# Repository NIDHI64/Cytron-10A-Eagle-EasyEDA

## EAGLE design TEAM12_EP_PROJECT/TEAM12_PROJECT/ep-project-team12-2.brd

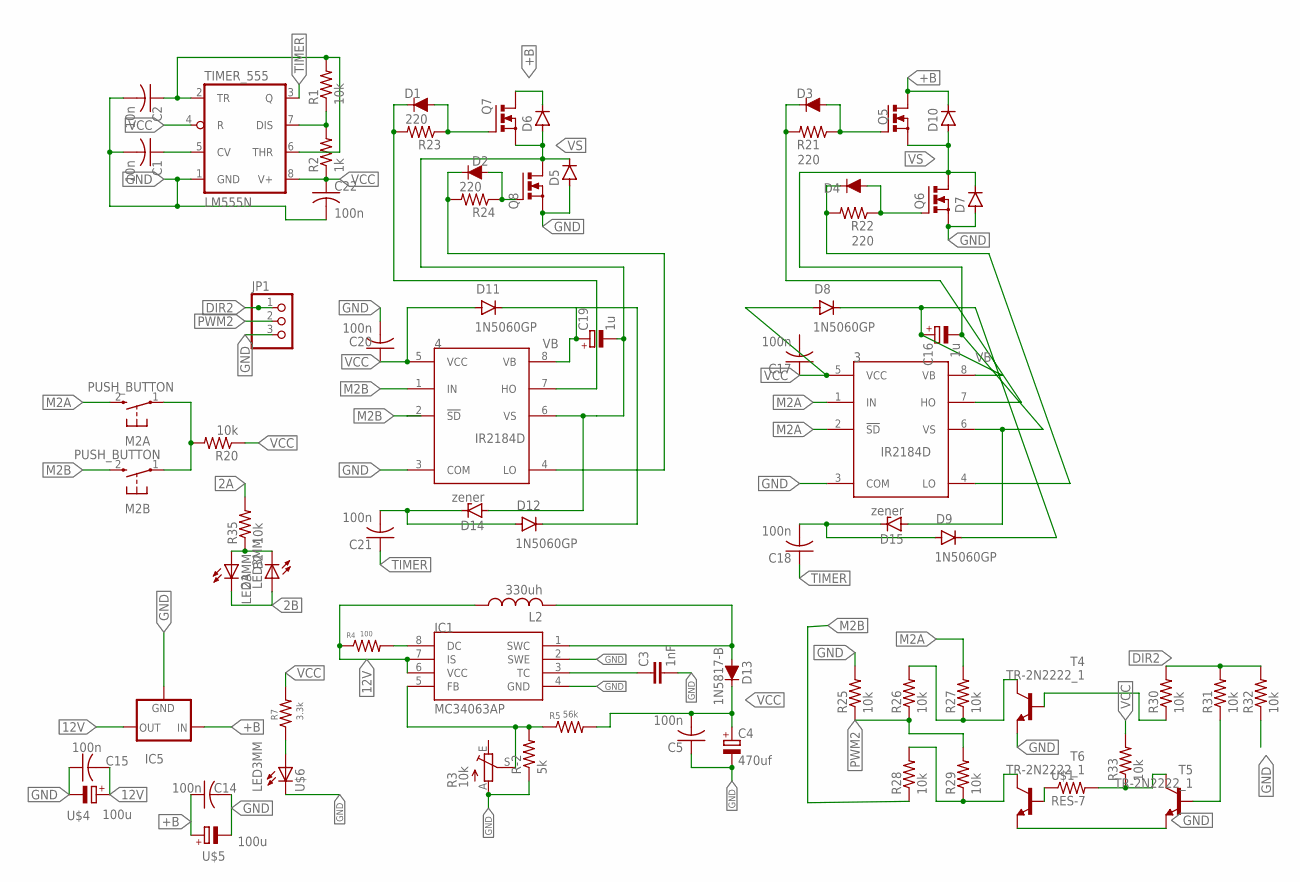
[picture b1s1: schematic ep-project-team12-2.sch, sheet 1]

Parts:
2A: LED3MM
3, 4: IR2184D; DIL08
B2: LED3MM
C1, C2: 10n; C025-025X050
C3: 1nF; C025-025X050
C4: 470uf; E3,5-8
C5, C14, C15, C17, C18, C20, C21, C22: 100n; C025-025X050
C16, C19: 1u; E5-5
D1, D2, D3, D4: 1A/50V/1.1V; DIODE-1N4001
D5, D6, D7, D10: BY396; DO201-15
D8, D9, D11, D12: 1N5060GP; DO15-12
D13: 1N5817-B; DIODE-1N4001
D14, D15: zener; SOD81
IC1: MC34063AP; DIL08
IC5: 78XXS
JP1: PINHD-3_DATA; 1X03_DATA
L2: 330uh; POWER-CHOKE_WE-TPC
M2A, M2B: PUSH_BUTTON; B3F-10XX
Q5, Q6, Q7, Q8: MOSFET_NTO220BV; TO220BV
R1, R20, R25, R26, R27, R28, R29, R30, R31, R32, R33, R35: 10k; 0204/7
R2: 1k; 0204/7
R3: 10k; CA6V
R4: 100; 0204/7
R5: 56k; 0204/7
R7: 3.3k; 0204/7
R21, R22, R23, R24: 220; 0204/7
R-2: 5k; 0204/7
T4, T5, T6: TR-2N2222_1; TO92-EBC
TIMER_555: LM555N; DIL08
U$1: RES-7; 0204/7
U$4, U$5: 100u; E3,5-8
U$6: LED3MM

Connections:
2A: R35.2
2B: 2A.K (C), B2.A
12V: C15.2, IC1.6 (VCC), IC1.7 (IS), IC5.OUT, L2.1, R4.1, U$4.+
+B: C14.1, D6.C, D10.C, IC5.IN, Q5.D, Q7.D, U$5.+
DIR2: JP1.1, R30.2, R31.2, R32.2
GND: 3.3 (COM), 4.3 (COM), C1.2, C2.2, C3.2, C4.-, C5.1, C14.2, C15.1, C20.2, C22.2, D5.A, D7.A, IC1.2 (SWE), IC1.4 (GND), IC5.GND, JP1.3, Q6.S, Q8.S, R3.A, R25.2, R32.1, R-2.1, T4.E, T5.E, T6.E, TIMER_555.1 (GND), U$4.-, U$5.-, U$6.K (C)
M2A: 3.1 (IN), 3.2 (!SD), M2A.2 (S), R27.2
M2B: 4.1 (IN), 4.2 (!SD), M2B.2 (S), R28.1
unnamed: C1.1, TIMER_555.5 (CV)
unnamed: R1.1, R2.2, TIMER_555.7 (DIS)
unnamed: C2.1, R1.2, TIMER_555.2 (TR), TIMER_555.6 (THR)
unnamed: D4.A, Q6.G, R22.1
unnamed: 3.4 (LO), D4.C, R22.2
unnamed: M2A.1, M2B.1, R20.2
unnamed: T6.B, U$1.1
unnamed: C3.1, IC1.3 (TC)
unnamed: D13.A, IC1.1 (SWC), L2.2
unnamed: 4.7 (HO), D1.C, R23.2
unnamed: IC1.5 (FB), R3.S, R5.1, R-2.2
unnamed: 4.4 (LO), D2.C, R24.2
unnamed: IC1.8 (DC), R4.2
unnamed: R7.1, U$6.A
unnamed: D3.A, Q5.G, R21.1
unnamed: 3.7 (HO), D3.C, R21.2
unnamed: C18.2, D9.A, D15.C
unnamed: D2.A, Q8.G, R24.1
unnamed: D1.A, Q7.G, R23.1
unnamed: C21.2, D12.A, D14.C
unnamed: R28.2, R29.1, T6.C
unnamed: R26.2, R27.1, T4.C
unnamed: R30.1, T4.B
unnamed: R33.1, T5.C, U$1.2
unnamed: R31.1, T5.B
unnamed: 2A.A, B2.K (C), R35.1
PWM2: JP1.2, R25.1, R26.1, R29.2
TIMER: C18.1, C21.1, TIMER_555.3 (Q)
VB: 3.8 (VB), 4.8 (VB), C16.+, C19.+, D8.C, D9.C, D11.C, D12.C
VCC: 3.5 (VCC), 4.5 (VCC), C4.+, C5.2, C17.1, C20.1, C22.1, D8.A, D11.A, D13.C, R2.1, R5.2, R7.2, R20.1, R33.2, TIMER_555.4 (R), TIMER_555.8 (V+)
VS: 3.6 (VS), 4.6 (VS), C16.-, C19.-, D5.C, D6.A, D7.C, D10.A, D14.A, D15.A, Q5.S, Q6.D, Q7.S, Q8.D

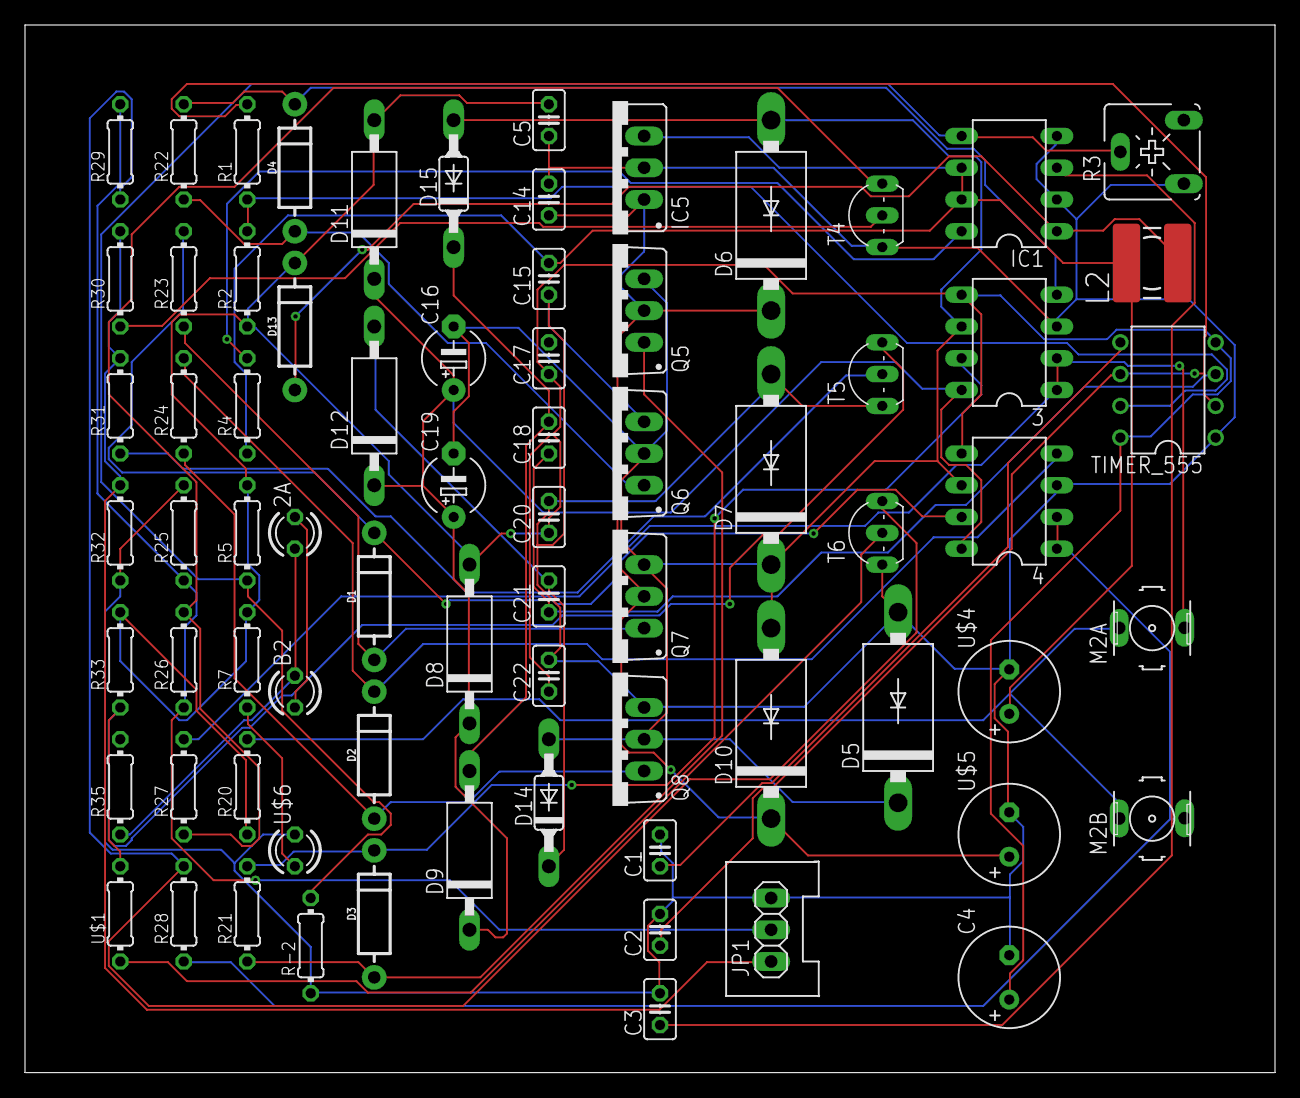
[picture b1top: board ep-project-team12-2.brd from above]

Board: 2 copper layers, 100.0 x 83.8 mm, 73 parts (0 on the bottom side), 38 nets.
